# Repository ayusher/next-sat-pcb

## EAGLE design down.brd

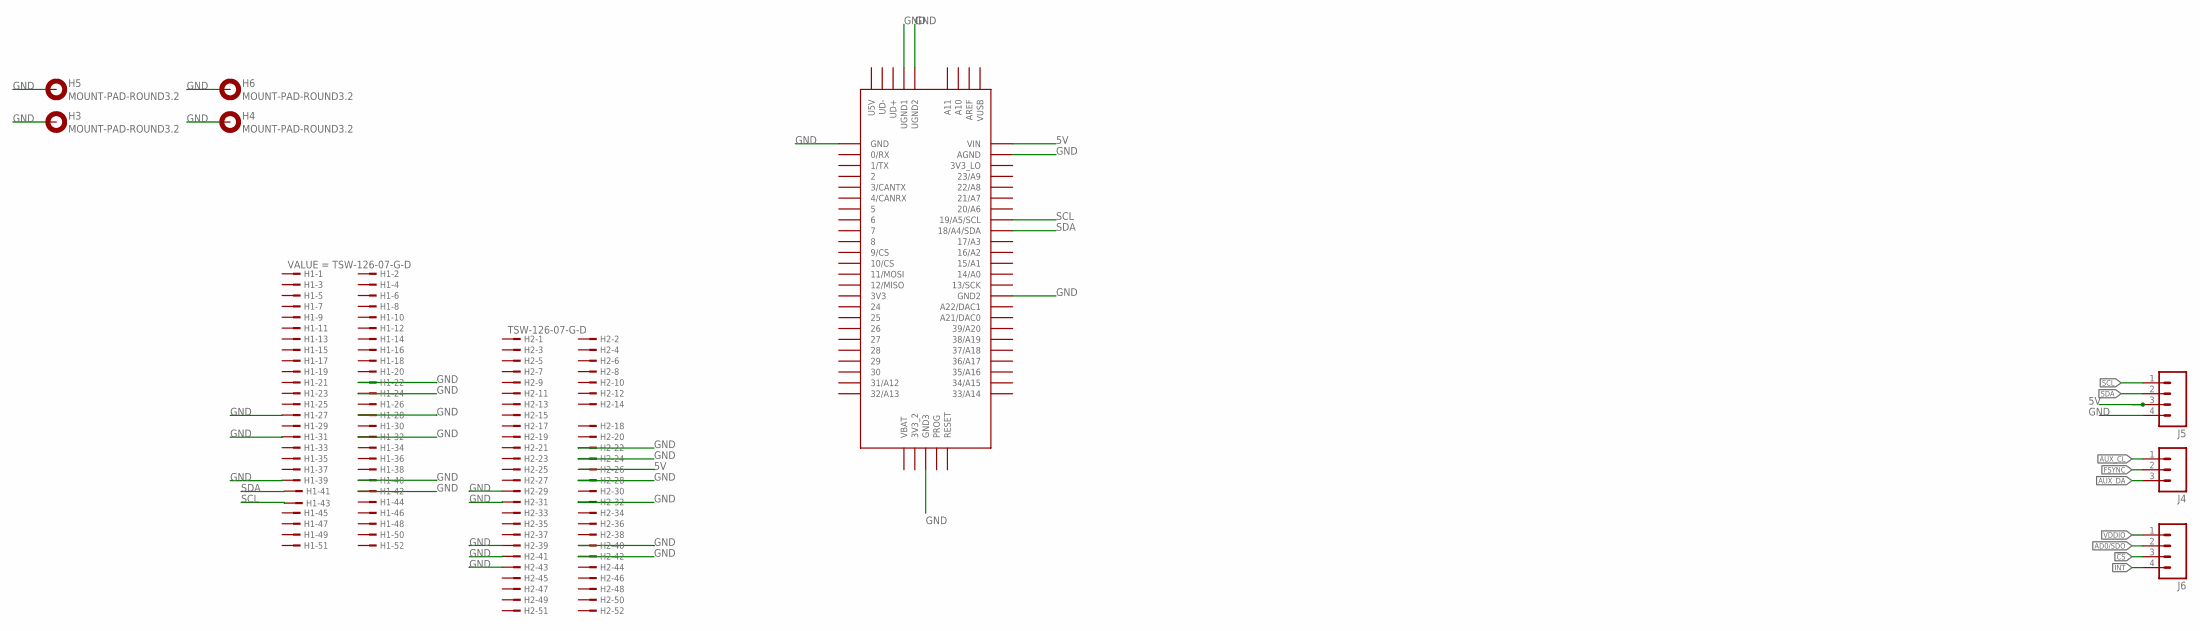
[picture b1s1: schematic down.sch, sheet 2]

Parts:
H1, H2: TSW-126-07-G-D; TSW-126-XX-G-D
H3, H4, H5, H6: MOUNT-PAD-ROUND3.2; 3,2-PAD
J4: M03PTH; 1X03
J5, J6: M04PTH; 1X04
U$1: TEENSY_3.5/3.6

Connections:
5V: H2.26, J5.3, U$1.VIN
!CS: J6.3
AD0/SDO: J6.2
AUX_CL: J4.1
AUX_DA: J4.3
FSYNC: J4.2
GND: H1.22, H1.24, H1.27, H1.28, H1.31, H1.32, H1.39, H1.40, H1.42, H2.22, H2.24, H2.28, H2.29, H2.31, H2.32, H2.39, H2.40, H2.41, H2.42, H2.43, H3.B3,2, H4.B3,2, H5.B3,2, H6.B3,2, J5.4, U$1.AGND, U$1.GND, U$1.GND2, U$1.GND3, U$1.UGND1, U$1.UGND2
INT: J6.4
SCL: H1.43, J5.1, U$1.19/A5/SCL
SDA: H1.41, J5.2, U$1.18/A4/SDA
VDDIO: J6.1

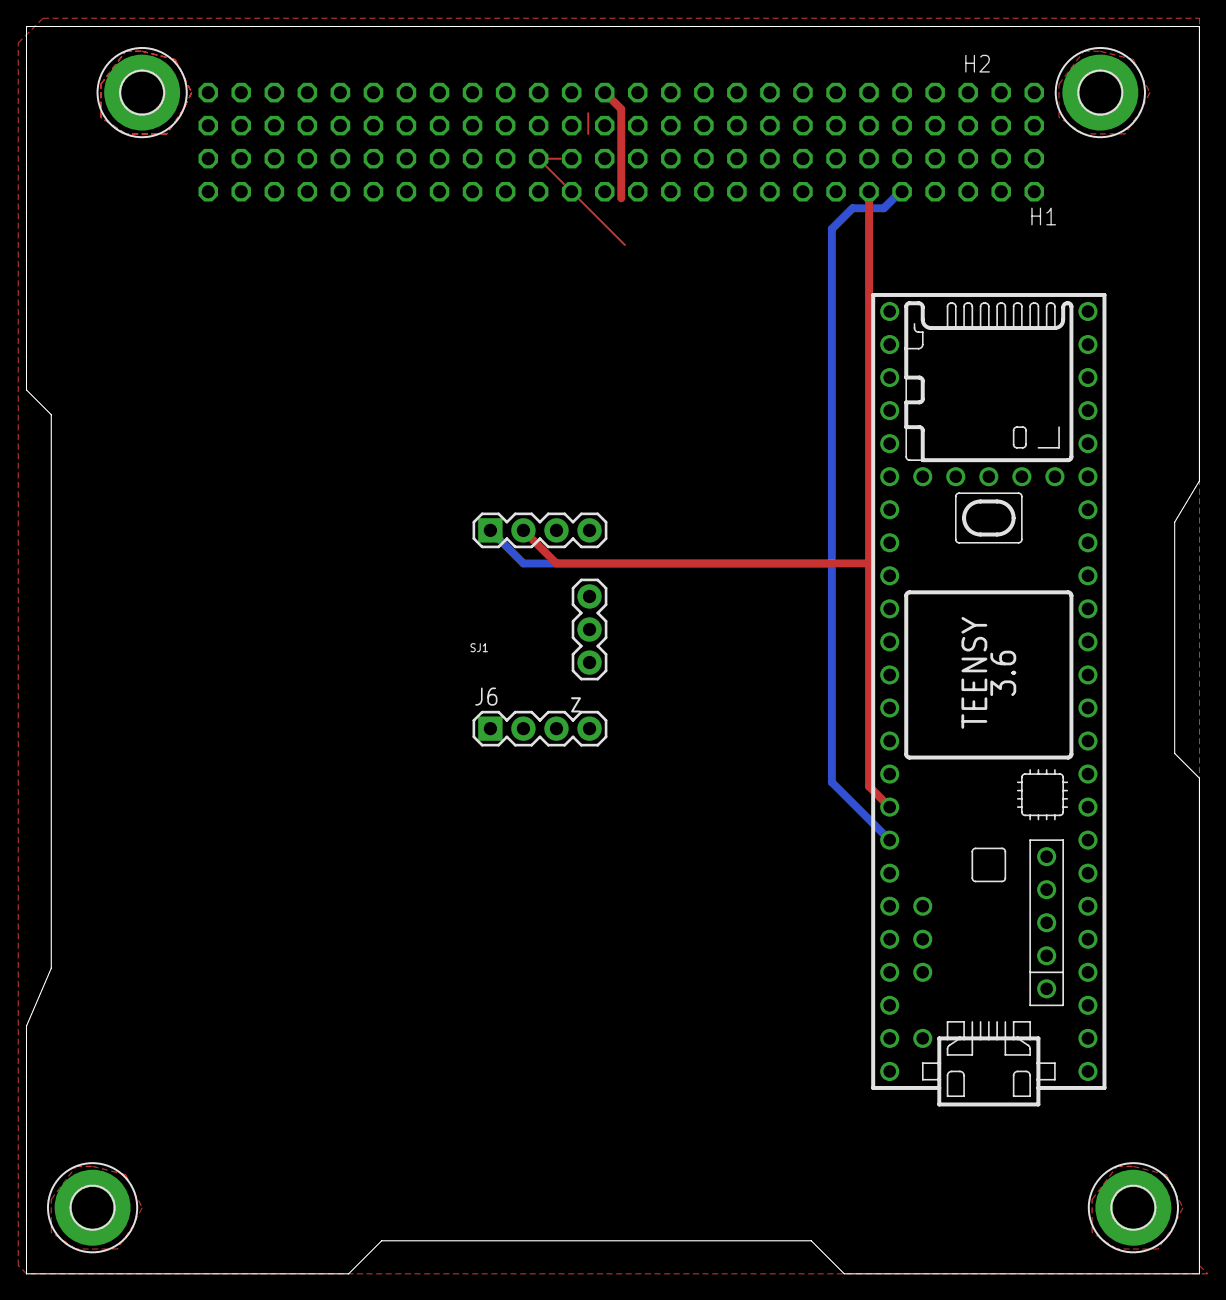
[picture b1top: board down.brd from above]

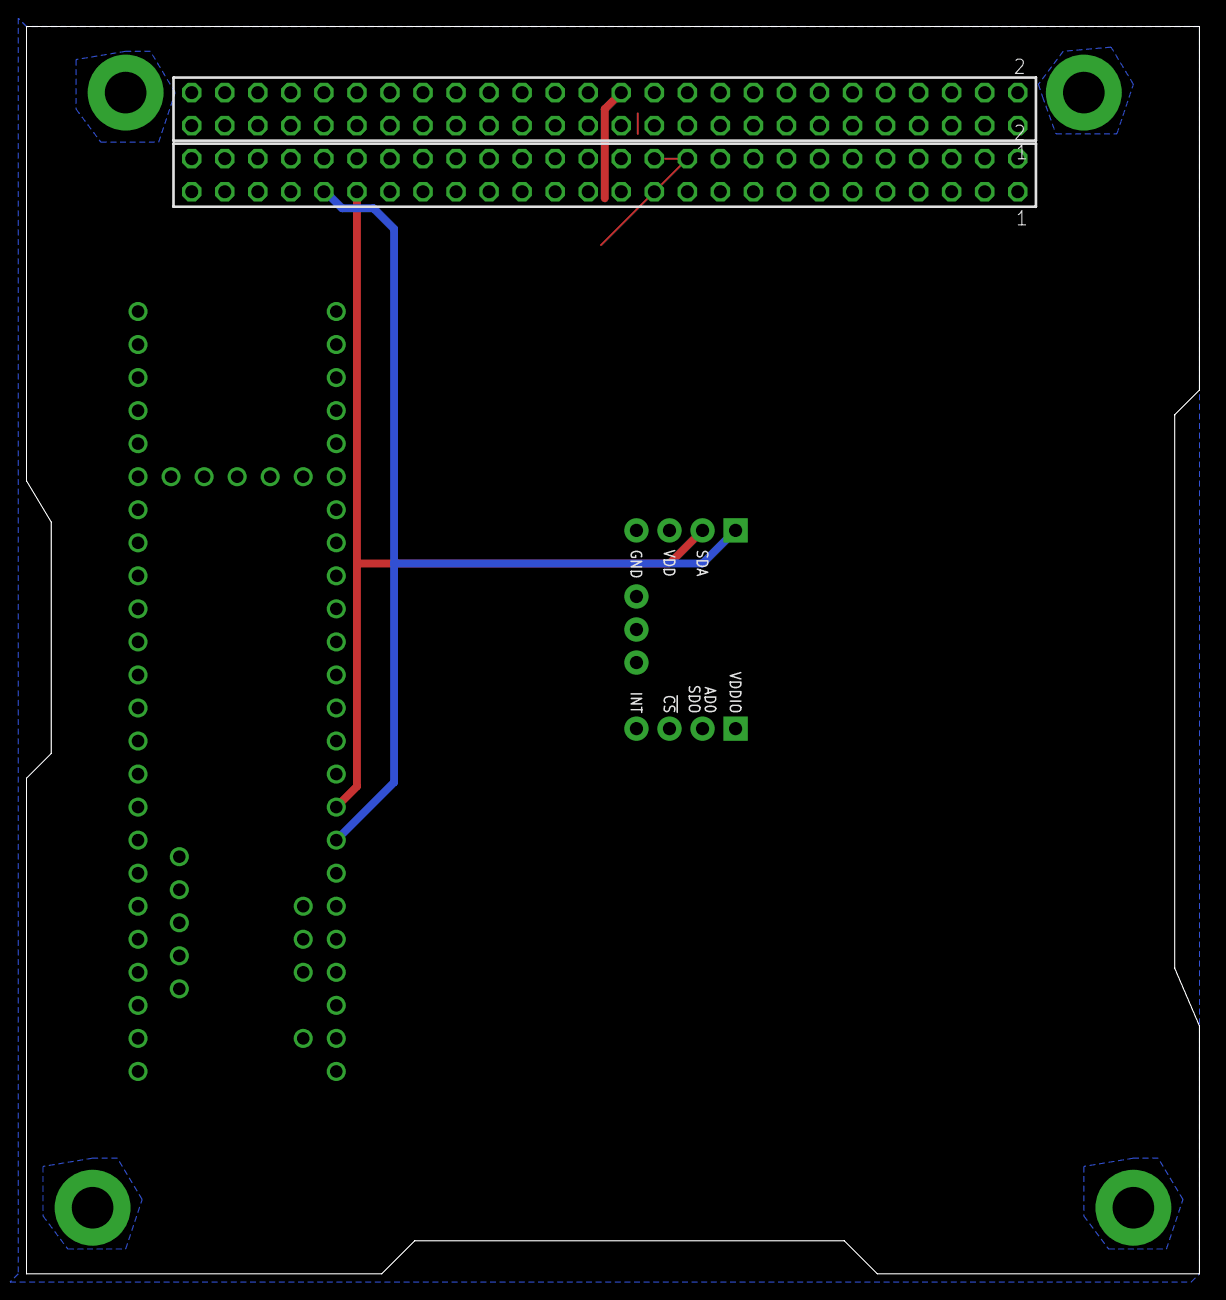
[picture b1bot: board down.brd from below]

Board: 2 copper layers, 90.2 x 95.9 mm, 10 parts (2 on the bottom side), 4 nets.

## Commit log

2020-03-26 Add EAGLE files
2020-03-26 IMU done

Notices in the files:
parts and their libraries:
SparkFun-Connectors: Licensing: Creative Commons ShareAlike 4.0 International - https://creativecommons.org/licenses/by-sa/4.0
